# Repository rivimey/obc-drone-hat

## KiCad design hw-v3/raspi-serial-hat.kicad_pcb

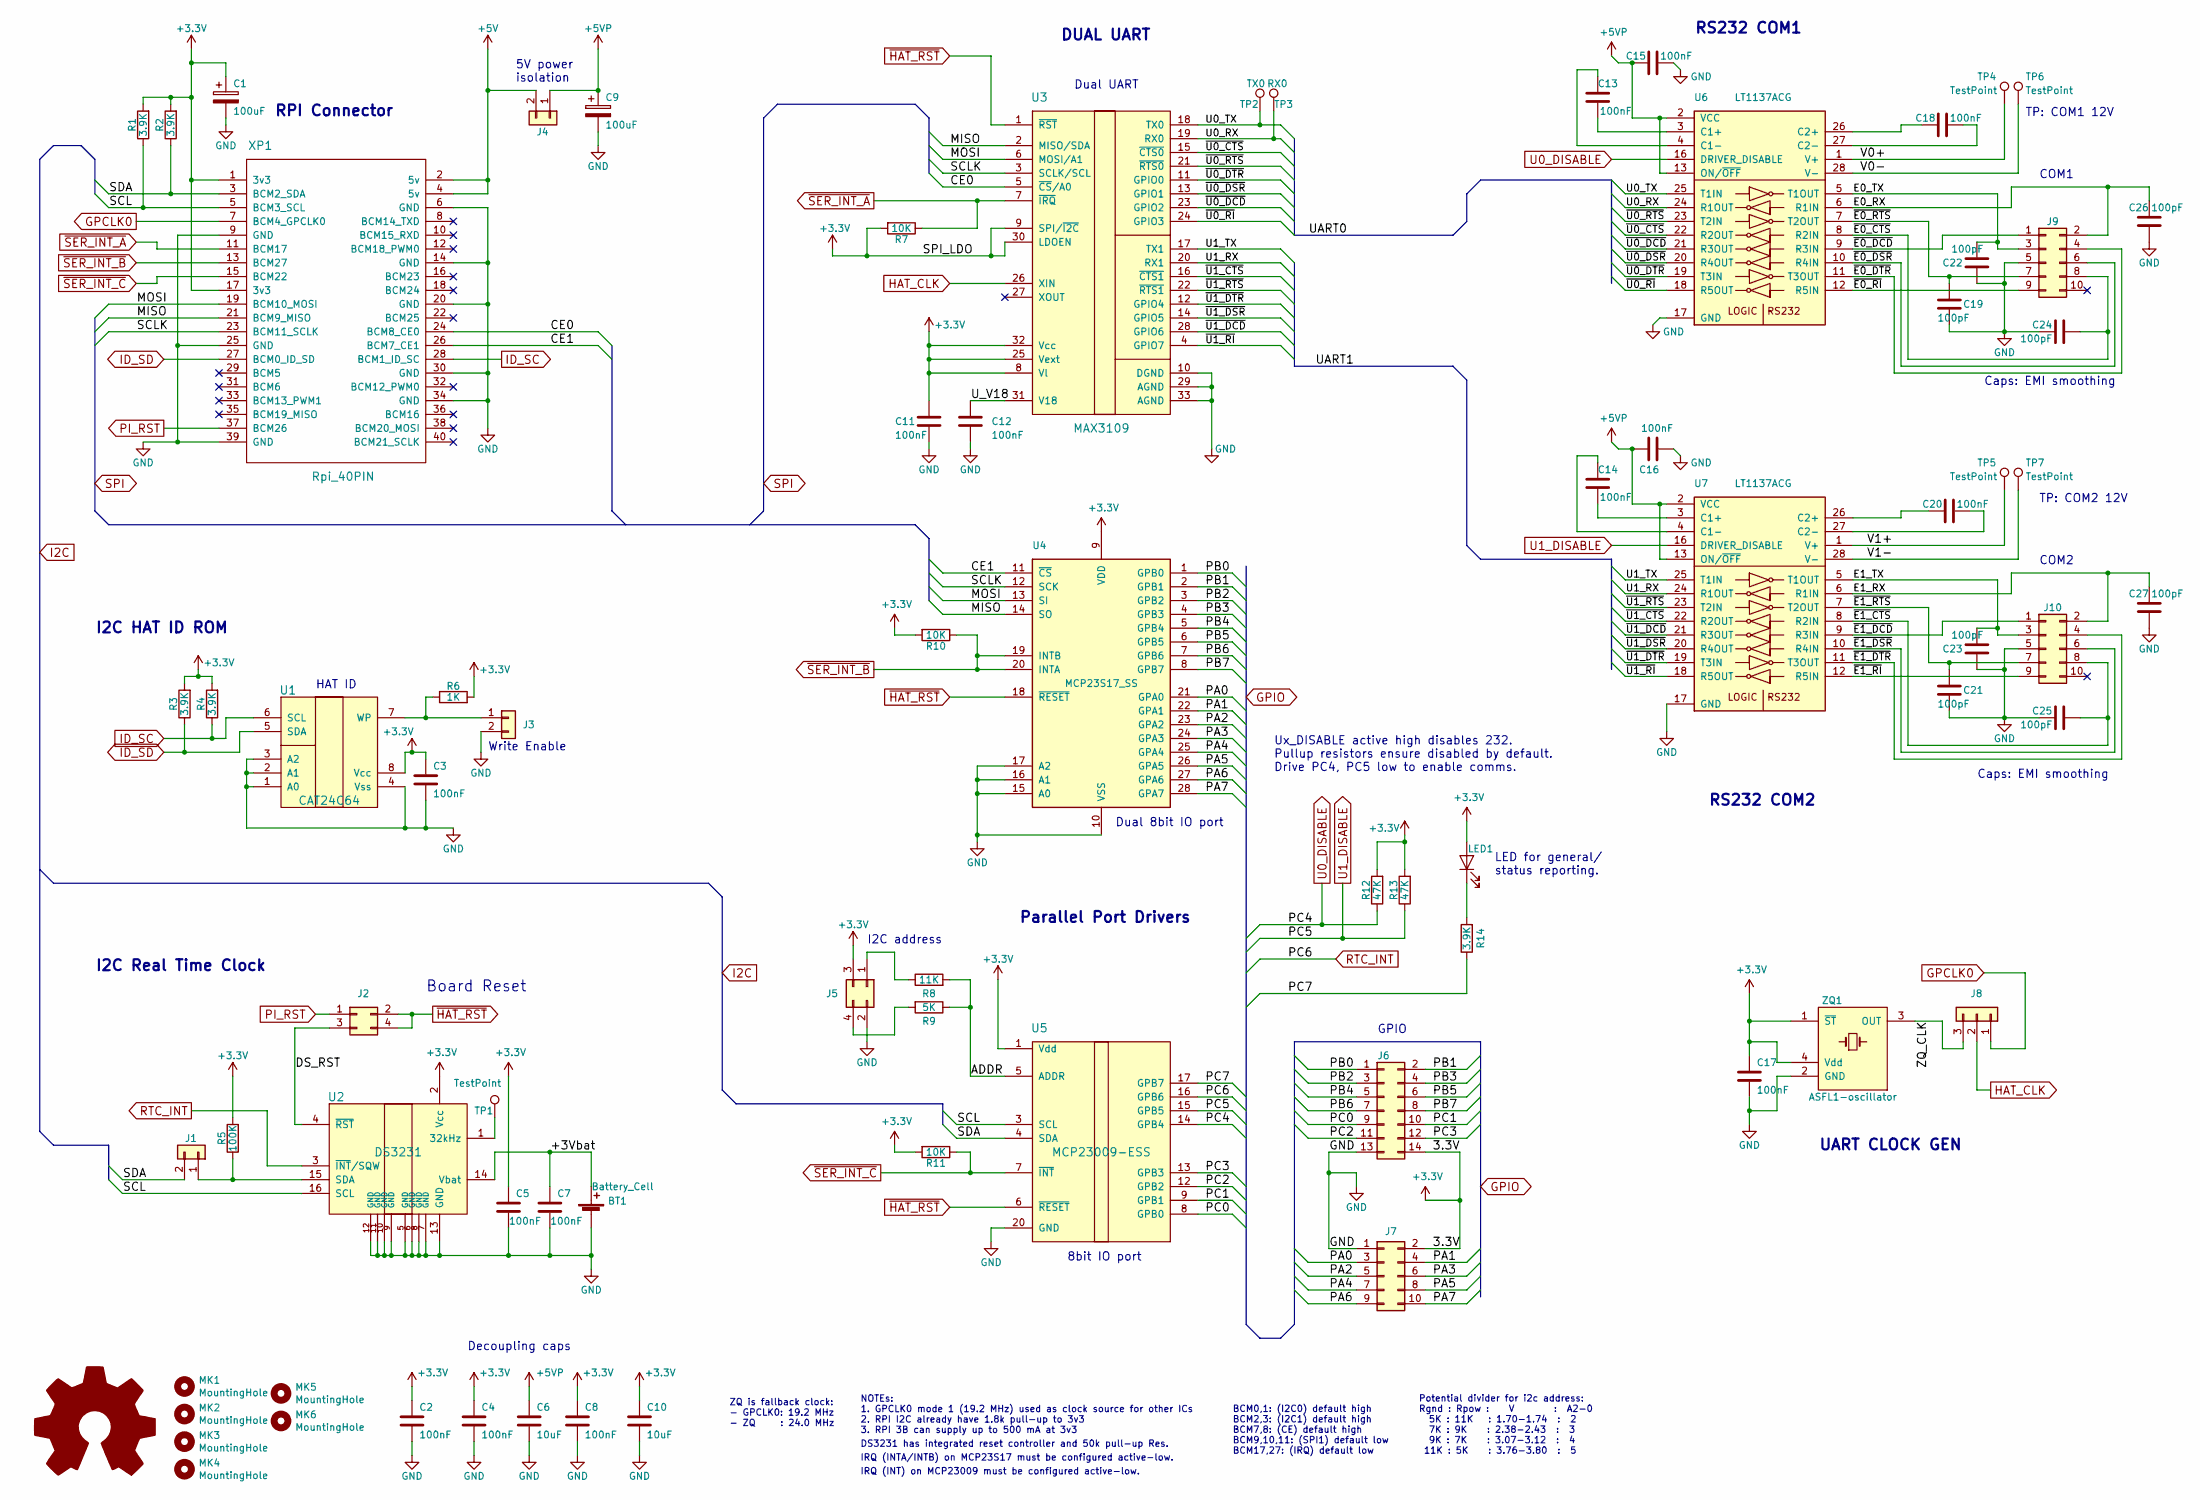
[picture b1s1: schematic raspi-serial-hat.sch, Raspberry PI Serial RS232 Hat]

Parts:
BT1: Battery_Cell; BatteryHolder_Keystone_500; Manuf Part No BAT-HLD-012-SMT
C1, C9: 100uF; CP_EIA-3528-12_Kemet-T_Pad1.50x2.35mm_HandSolder; Manuf Part No T520B107M010ATE070
C2, C3, C4, C5, C7, C8, C11, C12, C13, C14, C15, C16, C17, C18, C20: 100nF; C_0603_1608Metric_Pad1.05x0.95mm_HandSolder; Manuf Part No C0603C104K4RECTU
C6, C10: 10uF; C_0805_2012Metric_Pad1.15x1.40mm_HandSolder; Manuf Part No VJ0805G106KXYTW1BC
C19, C21, C22, C23, C24, C25, C26, C27: 100pF; C_0603_1608Metric_Pad1.05x0.95mm_HandSolder; Manuf Part No 885012206077
J1, J3, J4: Conn_01x02; PinHeader_1x02_P1.27mm_Vertical; Manuf Part No M50-3530242
J2, J5: Conn_02x02; PinHeader_2x02_P1.27mm_Vertical; Manuf Part No M50-3530242
J6: Conn_02x07; PinHeader_2x07_P2.54mm_Vertical; Manuf Part No 54102-S1007LF
J7: Conn_02x05_Odd_Even; PinHeader_2x05_P2.54mm_Vertical
J8: Conn_01x03; PinHeader_1x03_P1.27mm_Vertical; Manuf Part No M50-3530242
J9, J10: Conn_02x05_Odd_Even; IDC-Header_2x05_P2.54mm_Vertical; Manuf Part No 86130105014345E1LF
LED1: LED; LED_0603_1608Metric; Manuf Part No APT1608QGW
MK1, MK2, MK3, MK4, MK5, MK6: MountingHole; M2.5_Mounting_Hole
R1, R2, R3, R4, R14: 3.9K; R_0603_1608Metric_Pad1.05x0.95mm_HandSolder; Manuf Part No CRCW060310K0JNEAC
R5: 100K; R_0603_1608Metric_Pad1.05x0.95mm_HandSolder; Manuf Part No CRCW060310K0JNEAC
R6: 1K; R_0603_1608Metric_Pad1.05x0.95mm_HandSolder; Manuf Part No CRCW060310K0JNEAC
R7, R10, R11: 10K; R_0603_1608Metric_Pad1.05x0.95mm_HandSolder; Manuf Part No CRCW060310K0JNEAC
R8: 11K; R_0603_1608Metric_Pad1.05x0.95mm_HandSolder; Manuf Part No CRCW060310K0JNEAC
R9: 5K; R_0603_1608Metric_Pad1.05x0.95mm_HandSolder; Manuf Part No CRCW060310K0JNEAC
R12, R13: 47K; R_0603_1608Metric_Pad1.05x0.95mm_HandSolder; Manuf Part No CRCW060310K0JNEAC
TP1, TP4, TP5, TP6, TP7: TestPoint; TestPoint_Pad_1.0x1.0mm
TP2: TX0; TestPoint_Pad_1.0x1.0mm
TP3: RX0; TestPoint_Pad_1.0x1.0mm
U1: CAT24C64; SOIC-8_3.9x4.9mm_P1.27mm; Manuf Part No CAT24C64WI-GT3
U2: DS3231; SOIC-16W_7.5x10.3mm_P1.27mm; Manuf Part No DS3231S#T&R
U3: MAX3109; QFN-32-1EP_5x5mm_P0.5mm_EP3.45x3.45mm; Manuf Part No MAX3109ETJ+
U4: MCP23S17_SS; SSOP-28_5.3x10.2mm_P0.65mm; Manuf Part No MCP23S17T-E/SS
U5: MCP23009-ESS; SSOP-20_5.3x7.2mm_P0.65mm; Manuf Part No MCP23009-E/SS
U6, U7: LT1137ACG; SSOP-28_5.3x10.2mm_P0.65mm; Manuf Part No LT1137ACG#PBF
XP1: Rpi_40PIN; RaspberryPi-40Pin_P2.54mm; Manuf Part No 1112
ZQ1: ASFL1-oscillator; Crystal_SMD_Abracon_ABM3B-4Pin_5.0x3.2mm; Manuf Part No ASFL1-24.000MHZ-EC-T

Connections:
+3V3: C1.1, C2.1, C3.1, C4.1, C5.1, C8.1, C10.1, C11.1, C17.1, J5.3, J6.14, J7.2, LED1.2 (A), R1.2, R2.2, R3.2, R4.2, R5.2, R6.2, R7.2, R10.2, R11.2, R12.2, R13.2, U1.8 (Vcc), U2.2 (Vcc), U3.8 (Vl), U3.9 (SPI/~I2C), U3.25 (Vext), U3.30 (LDOEN), U3.32 (Vcc), U4.9 (VDD), U5.1 (Vdd), XP1.1 (3v3), XP1.17 (3v3), ZQ1.1 (~ST), ZQ1.4 (Vdd)
+5V: J4.2, XP1.2 (5v), XP1.4 (5v)
+5VP: C6.1, C9.1, C15.2, C16.1, J4.1, U6.2 (VCC), U6.13 (ON/~OFF), U7.2 (VCC), U7.13 (ON/~OFF)
/+3Vbat: BT1.1 (+), C7.1, U2.14 (Vbat)
/ADDR: R8.2, R9.1, U5.5 (ADDR)
/CE0: U3.5 (~CS~/A0), XP1.24 (BCM8_CE0)
/CE1: U4.11 (~CS~), XP1.26 (BCM7_CE1)
/DS_RST: J2.3, U2.4 (~RST)
/E0_RX: C26.2, J9.2, U6.6 (R1IN)
/E0_TX: C22.2, J9.3, U6.5 (T1OUT)
/E1_RX: C27.2, J10.2, U7.6 (R1IN)
/E1_TX: C23.2, J10.3, U7.5 (T1OUT)
/MISO: U3.2 (MISO/SDA), U4.14 (SO), XP1.21 (BCM9_MISO)
/MOSI: U3.6 (MOSI/A1), U4.13 (SI), XP1.19 (BCM10_MOSI)
/PA0: J7.3, U4.21 (GPA0)
/PA1: J7.4, U4.22 (GPA1)
/PA2: J7.5, U4.23 (GPA2)
/PA3: J7.6, U4.24 (GPA3)
/PA4: J7.7, U4.25 (GPA4)
/PA5: J7.8, U4.26 (GPA5)
/PA6: J7.9, U4.27 (GPA6)
/PA7: J7.10, U4.28 (GPA7)
/PB0: J6.1, U4.1 (GPB0)
/PB1: J6.2, U4.2 (GPB1)
/PB2: J6.3, U4.3 (GPB2)
/PB3: J6.4, U4.4 (GPB3)
/PB4: J6.5, U4.5 (GPB4)
/PB5: J6.6, U4.6 (GPB5)
/PB6: J6.7, U4.7 (GPB6)
/PB7: J6.8, U4.8 (GPB7)
/PC0: J6.9, U5.8 (GPB0)
/PC1: J6.10, U5.9 (GPB1)
/PC2: J6.11, U5.12 (GPB2)
/PC3: J6.12, U5.13 (GPB3)
/PC7: R14.1, U5.17 (GPB7)
/SCL: R1.1, U2.16 (SCL), U5.3 (SCL), XP1.5 (BCM3_SCL)
/SCLK: U3.3 (SCLK/SCL), U4.12 (SCK), XP1.23 (BCM11_SCLK)
/SDA: J1.2, R2.1, U5.4 (SDA), XP1.3 (BCM2_SDA)
/U0_RX: TP3.1, U3.19 (RX0), U6.24 (R1OUT)
/U0_TX: TP2.1, U3.18 (TX0), U6.25 (T1IN)
/U1_RX: U3.20 (RX1), U7.24 (R1OUT)
/U1_TX: U3.17 (TX1), U7.25 (T1IN)
/U_V18: C12.1, U3.31 (V18)
/V0+: TP4.1, U6.1 (V+)
/V0-: TP6.1, U6.28 (V-)
/V1+: TP5.1, U7.1 (V+)
/V1-: TP7.1, U7.28 (V-)
/ZQ_CLK: J8.3, ZQ1.3 (OUT)
/~E0_CTS: C24.2, J9.8, U6.8 (R2IN)
/~E0_DCD: J9.1, U6.9 (R3IN)
/~E0_DSR: J9.6, U6.10 (R4IN)
/~E0_DTR: J9.4, U6.11 (T3OUT)
/~E0_RI: J9.9, U6.12 (R5IN)
/~E0_RTS: C19.2, J9.7, U6.7 (T2OUT)
/~E1_CTS: C25.2, J10.8, U7.8 (R2IN)
/~E1_DCD: J10.1, U7.9 (R3IN)
/~E1_DSR: J10.6, U7.10 (R4IN)
/~E1_DTR: J10.4, U7.11 (T3OUT)
/~E1_RI: J10.9, U7.12 (R5IN)
/~E1_RTS: C21.2, J10.7, U7.7 (T2OUT)
/~U0_CTS: U3.15 (~CTS0), U6.22 (R2OUT)
/~U0_DCD: U3.23 (GPIO2), U6.21 (R3OUT)
/~U0_DSR: U3.13 (GPIO1), U6.20 (R4OUT)
/~U0_DTR: U3.11 (GPIO0), U6.19 (T3IN)
/~U0_RI: U3.24 (GPIO3), U6.18 (R5OUT)
/~U0_RTS: U3.21 (~RTS0), U6.23 (T2IN)
/~U1_CTS: U3.16 (~CTS1), U7.22 (R2OUT)
/~U1_DCD: U3.28 (GPIO6), U7.21 (R3OUT)
/~U1_DSR: U3.14 (GPIO5), U7.20 (R4OUT)
/~U1_DTR: U3.12 (GPIO4), U7.19 (T3IN)
/~U1_RI: U3.4 (GPIO7), U7.18 (R5OUT)
/~U1_RTS: U3.22 (~RTS1), U7.23 (T2IN)
GND: BT1.2 (-), C1.2, C2.2, C3.2, C4.2, C5.2, C6.2, C7.2, C8.2, C9.2, C10.2, C11.2, C12.2, C15.1, C16.2, C17.2, C19.1, C21.1, C22.1, C23.1, C24.1, C25.1, C26.1, C27.1, J3.2, J5.2, J6.13, J7.1, J9.5, J10.5, U1.1 (A0), U1.2 (A1), U1.3 (A2), U1.4 (Vss), U2.5 (GND), U2.6 (GND), U2.7 (GND), U2.8 (GND), U2.9 (GND), U2.10 (GND), U2.11 (GND), U2.12 (GND), U2.13 (GND), U3.10 (DGND), U3.29 (AGND), U3.33 (AGND), U4.10 (VSS), U4.15 (A0), U4.16 (A1), U4.17 (A2), U5.20 (GND), U6.17 (GND), U7.17 (GND), XP1.6 (GND), XP1.9 (GND), XP1.14 (GND), XP1.20 (GND), XP1.25 (GND), XP1.30 (GND), XP1.34 (GND), XP1.39 (GND), ZQ1.2 (GND)
GPCLK0: J8.1, XP1.7 (BCM4_GPCLK0)
HAT_CLK: J8.2, U3.26 (XIN)
ID_SC: R4.1, U1.6 (SCL), XP1.28 (BCM1_ID_SC)
ID_SD: R3.1, U1.5 (SDA), XP1.27 (BCM0_ID_SD)
unnamed: C13.1, U6.3 (C1+)
unnamed: C13.2, U6.4 (C1-)
unnamed: C14.1, U7.3 (C1+)
unnamed: C14.2, U7.4 (C1-)
unnamed: C18.1, U6.27 (C2-)
unnamed: C18.2, U6.26 (C2+)
unnamed: C20.1, U7.27 (C2-)
unnamed: C20.2, U7.26 (C2+)
unnamed: J1.1, R5.1, U2.15 (SDA)
unnamed: J3.1, R6.1, U1.7 (WP)
unnamed: J5.1, R8.1
unnamed: J5.4, R9.2
unnamed: LED1.1 (K), R14.2
unnamed: TP1.1, U2.1 (32kHz)
PI_RST: J2.1, XP1.37 (BCM26)
RTC_INT: U2.3 (~INT~/SQW), U5.16 (GPB6)
U0_DISABLE: R12.1, U5.14 (GPB4), U6.16 (DRIVER_DISABLE)
U1_DISABLE: R13.1, U5.15 (GPB5), U7.16 (DRIVER_DISABLE)
~HAT_RST: J2.2, J2.4, U3.1 (~RST), U4.18 (~RESET~), U5.6 (~RESET)
~SER_INT_A: R7.1, U3.7 (~IRQ), XP1.11 (BCM17)
~SER_INT_B: R10.1, U4.19 (INTB), U4.20 (INTA), XP1.13 (BCM27)
~SER_INT_C: R11.1, U5.7 (~INT), XP1.15 (BCM22)

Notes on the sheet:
DS3231 has integrated reset controller and 50k pull-up Res.
NOTEs: 1. GPCLK0 mode 1 (19.2 MHz) used as clock source for other ICs 2. RPI I2C already have 1.8k pull-up to 3v3 3. RPI 3B can supply up to 500 mA at 3v3
ZQ is fallback clock: - GPCLK0: 19.2 MHz - ZQ : 24.0 MHz
HAT ID
Decoupling caps
GPIO
Dual UART
TP: COM1 12V
Dual 8bit IO port
8bit IO port
RPI Connector
IRQ (INTA/INTB) on MCP23S17 must be configured active-low.
IRQ (INT) on MCP23009 must be configured active-low.
I2C address
COM1
BCM0,1: (I2C0) default high BCM2,3: (I2C1) default high BCM7,8: (CE) default high BCM9,10,11: (SPI1) default low BCM17,27: (IRQ) default low
5V power isolation
I2C HAT ID ROM
RS232 COM1
RS232 COM2
Caps: EMI smoothing
COM2
TP: COM2 12V
UART CLOCK GEN
DUAL UART
Parallel Port Drivers
Write Enable
Board Reset
Ux_DISABLE active high disables 232. Pullup resistors ensure disabled by default. Drive PC4, PC5 low to enable comms.
LED for general/ status reporting.
I2C Real Time Clock
Potential divider for i2c address: Rgnd : Rpow : V : A2-0 5K : 11K : 1.70-1.74 : 2 7K : 9K : 2.38-2.43 : 3 9K : 7K : 3.07-3.12 : 4 11K : 5K : 3.76-3.80 : 5

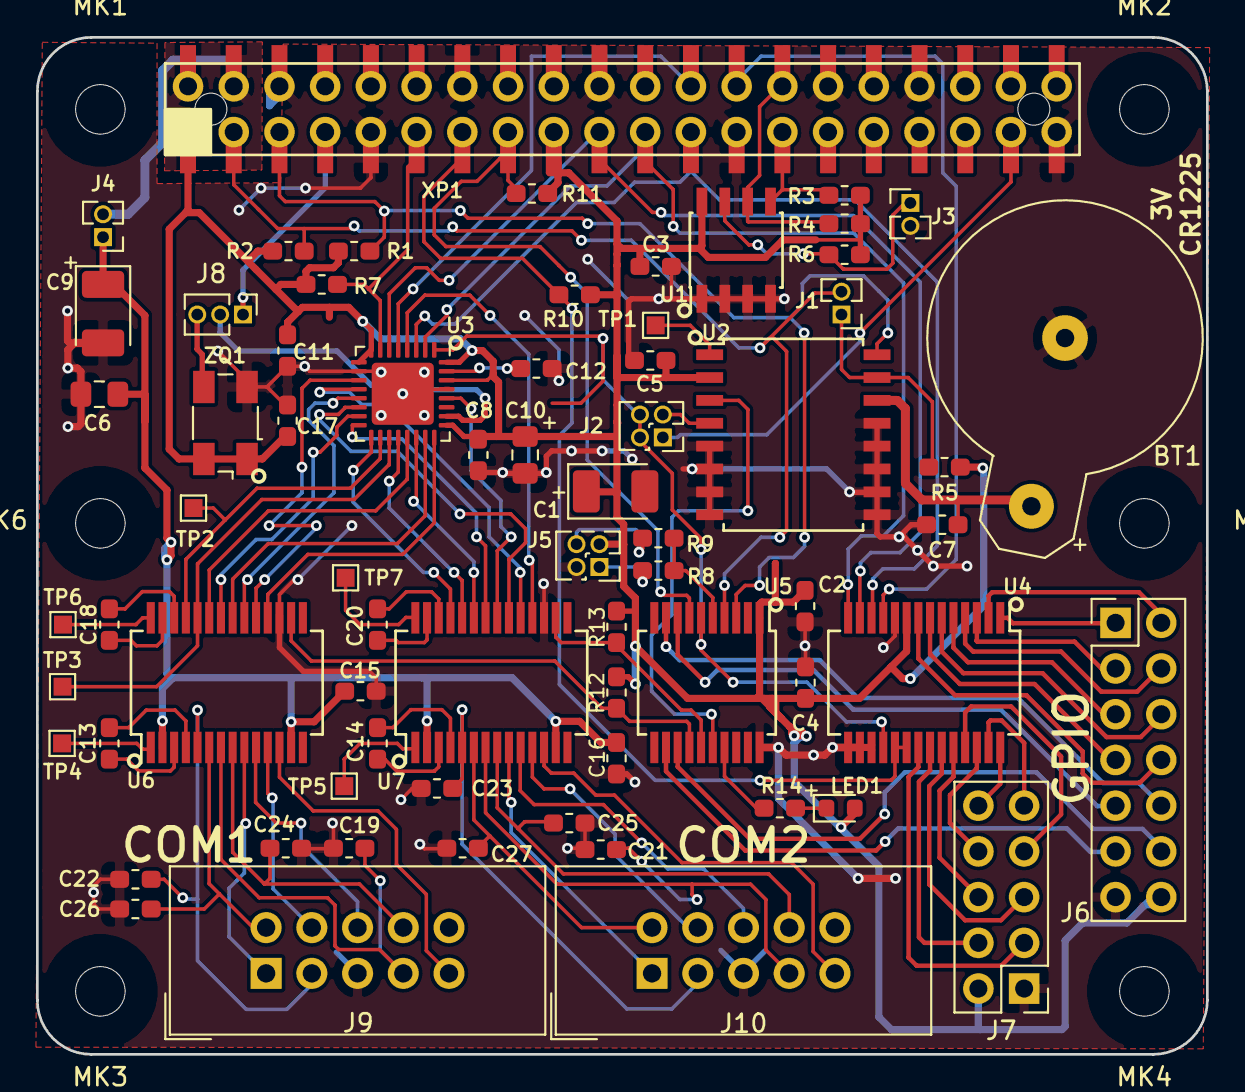
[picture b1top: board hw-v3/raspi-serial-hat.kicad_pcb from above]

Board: 2 copper layers, 65.0 x 56.5 mm, 75 parts (0 on the bottom side), 99 nets.

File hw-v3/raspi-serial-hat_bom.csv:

Source,/Users/ruth/Electronics/raspi-serial-hat/hw-v3/raspi-serial-hat.sch
Kicad Rev,Eeschema (5.1.4-0)
Generated Date,Tuesday, 15 October 2019 at 23:43:15

Title,Raspberry PI Serial RS232 Hat
Company,IvimeyCom
Revision,3
Date Issue,2019-10-08
Comment,IC-SERHAT-v3

Reference,Value,Cost/item,Manuf Part No,Manufacturer,Stock Number,Supplier,Library,Library Ref
BT1,Battery_Cell,0.221,BAT-HLD-012-SMT,Linx Technologies,712-BAT-HLD-012-SMT,Mouser,Device,Battery_Cell
C1,100uF,1.14,T520B107M010ATE070,KEMET,80-T520B107M10ATE070 ,Mouser,Device,CP
C10,10uF,0.30,VJ0805G106KXYTW1BC ,Vishay / Vitramon,77-VJ805G106KXYTW1BC ,Mouser,Device,C
C11,100nF,0.084,C0603C104K4RECTU,KEMET,80-C0603C104K4RECTU,Mouser,Device,C
C12,100nF,0.084,C0603C104K4RECTU,KEMET,80-C0603C104K4RECTU,Mouser,Device,C
C13,100nF,0.084,C0603C104K4RECTU,KEMET,80-C0603C104K4RECTU,Mouser,Device,C
C14,100nF,0.084,C0603C104K4RECTU,KEMET,80-C0603C104K4RECTU,Mouser,Device,C
C15,100nF,0.084,C0603C104K4RECTU,KEMET,80-C0603C104K4RECTU,Mouser,Device,C
C16,100nF,0.084,C0603C104K4RECTU,KEMET,80-C0603C104K4RECTU,Mouser,Device,C
C17,100nF,0.084,C0603C104K4RECTU,KEMET,80-C0603C104K4RECTU,Mouser,Device,C
C18,100nF,0.084,C0603C104K4RECTU,KEMET,80-C0603C104K4RECTU,Mouser,Device,C
C19,100pF,0.035,885012206077,Wurth Electronics,710-885012206077,Mouser,Device,C
C2,100nF,0.084,C0603C104K4RECTU,KEMET,80-C0603C104K4RECTU,Mouser,Device,C
C20,100nF,0.084,C0603C104K4RECTU,KEMET,80-C0603C104K4RECTU,Mouser,Device,C
C21,100pF,0.035,885012206077,Wurth Electronics,710-885012206077,Mouser,Device,C
C22,100pF,0.035,885012206077,Wurth Electronics,710-885012206077,Mouser,Device,C
C23,100pF,0.035,885012206077,Wurth Electronics,710-885012206077,Mouser,Device,C
C24,100pF,0.035,885012206077,Wurth Electronics,710-885012206077,Mouser,Device,C
C25,100pF,0.035,885012206077,Wurth Electronics,710-885012206077,Mouser,Device,C
C26,100pF,0.035,885012206077,Wurth Electronics,710-885012206077,Mouser,Device,C
C27,100pF,0.035,885012206077,Wurth Electronics,710-885012206077,Mouser,Device,C
C3,100nF,0.084,C0603C104K4RECTU,KEMET,80-C0603C104K4RECTU,Mouser,Device,C
C4,100nF,0.084,C0603C104K4RECTU,KEMET,80-C0603C104K4RECTU,Mouser,Device,C
C5,100nF,0.084,C0603C104K4RECTU,KEMET,80-C0603C104K4RECTU,Mouser,Device,C
C6,10uF,0.30,VJ0805G106KXYTW1BC ,Vishay / Vitramon,77-VJ805G106KXYTW1BC ,Mouser,Device,C
C7,100nF,0.084,C0603C104K4RECTU,KEMET,80-C0603C104K4RECTU,Mouser,Device,C
C8,100nF,0.084,C0603C104K4RECTU,KEMET,80-C0603C104K4RECTU,Mouser,Device,C
C9,100uF,1.14,T520B107M010ATE070,KEMET,80-T520B107M10ATE070 ,Mouser,Device,CP
J1,Conn_01x02,0.084,M50-3530242,Harwin,855-M50-3530242,Mouser,Connector_Generic,Conn_01x02
J10,Conn_02x05_Odd_Even,0.343,86130105014345E1LF,Amphenol FCI,649-861315014345E1LF,Mouser,Connector_Generic,Conn_02x05_Odd_Even
J2,Conn_02x02,0.084,M50-3530242,Harwin,855-M50-3530242,Mouser,Connector_Generic,Conn_02x02_Odd_Even
J3,Conn_01x02,0.084,M50-3530242,Harwin,855-M50-3530242,Mouser,Connector_Generic,Conn_01x02
J4,Conn_01x02,0.084,M50-3530242,Harwin,855-M50-3530242,Mouser,Connector_Generic,Conn_01x02
J5,Conn_02x02,0.084,M50-3530242,Harwin,855-M50-3530242,Mouser,Connector_Generic,Conn_02x02_Odd_Even
J6,Conn_02x07,0.481,54102-S1007LF,Amphenol FCI,649-54102-S1007LF,Mouser,Connector_Generic,Conn_02x07_Odd_Even
J7,Conn_02x05_Odd_Even,Connector_Generic,Conn_02x05_Odd_Even
J8,Conn_01x03,0.084,M50-3530242,Harwin,855-M50-3530242,Mouser,Connector_Generic,Conn_01x03
J9,Conn_02x05_Odd_Even,0.343,86130105014345E1LF,Amphenol FCI,649-861315014345E1LF,Mouser,Connector_Generic,Conn_02x05_Odd_Even
LED1,LED,Device,LED
R1,3.9K,0.076,CRCW060310K0JNEAC,Vishay,71-CRCW060310K0JNEAC,Mouser,Device,R
R10,10K,0.076,CRCW060310K0JNEAC,Vishay,71-CRCW060310K0JNEAC,Mouser,Device,R
R11,10K,0.076,CRCW060310K0JNEAC,Vishay,71-CRCW060310K0JNEAC,Mouser,Device,R
R12,47K,0.076,CRCW060310K0JNEAC,Vishay,71-CRCW060310K0JNEAC,Mouser,Device,R
R13,47K,0.076,CRCW060310K0JNEAC,Vishay,71-CRCW060310K0JNEAC,Mouser,Device,R
R14,3.9K,0.076,CRCW060310K0JNEAC,Vishay,71-CRCW060310K0JNEAC,Mouser,Device,R
R2,3.9K,0.076,CRCW060310K0JNEAC,Vishay,71-CRCW060310K0JNEAC,Mouser,Device,R
R3,3.9K,0.076,CRCW060310K0JNEAC,Vishay,71-CRCW060310K0JNEAC,Mouser,Device,R
R4,3.9K,0.076,CRCW060310K0JNEAC,Vishay,71-CRCW060310K0JNEAC,Mouser,Device,R
R5,100K,0.076,CRCW060310K0JNEAC,Vishay,71-CRCW060310K0JNEAC,Mouser,Device,R
R6,1K,0.076,CRCW060310K0JNEAC,Vishay,71-CRCW060310K0JNEAC,Mouser,Device,R
R7,10K,0.076,CRCW060310K0JNEAC,Vishay,71-CRCW060310K0JNEAC,Mouser,Device,R
R8,11K,0.076,CRCW060310K0JNEAC,Vishay,71-CRCW060310K0JNEAC,Mouser,Device,R
R9,5K,0.076,CRCW060310K0JNEAC,Vishay,71-CRCW060310K0JNEAC,Mouser,Device,R
U1,CAT24C64,,CAT24C64WI-GT3,ON Semiconductor,698-CAT24C64WI-GT3,Mouser,hat-ic,CAT24
U2,DS3231,6.00,DS3231S#T&R,Maxim Integrated,700-DS3231S#T&R- ,Mouser,hat-ic,DS3231
U3,MAX3109,5.21,MAX3109ETJ+,Maxim Integrated,700-MAX3109ETJ+,Mouser,hat-ic,MAX3109
U4,MCP23S17_SS,1.03,MCP23S17T-E/SS,Microchip Technology,579-MCP23S17T-E/SS,Mouser,Interface_Expansion,MCP23S17_SS
U5,MCP23009-ESS,0.882,MCP23009-E/SS,Microchip Technology,579-MCP23009-E/SS,Mouser,hat-ic,MCP23009-ESS
U6,LT1137ACG,6.07,LT1137ACG#PBF,Analog Devices,584-LT1137ACG#PBF,Mouser,uarts,LT1137ACG
U7,LT1137ACG,6.07,LT1137ACG#PBF,Analog Devices,584-LT1137ACG#PBF,Mouser,uarts,LT1137ACG
XP1,Rpi_40PIN,1.49,1112,Adafruit,485-1112,Mouser,rpi-conn,Rpi_40PIN
ZQ1,ASFL1-oscillator,0.944,ASFL1-24.000MHZ-EC-T,ABRACON,815-ASFL1-24.0-EC-T,Mouser,hat-ic,ASFL1-oscillator

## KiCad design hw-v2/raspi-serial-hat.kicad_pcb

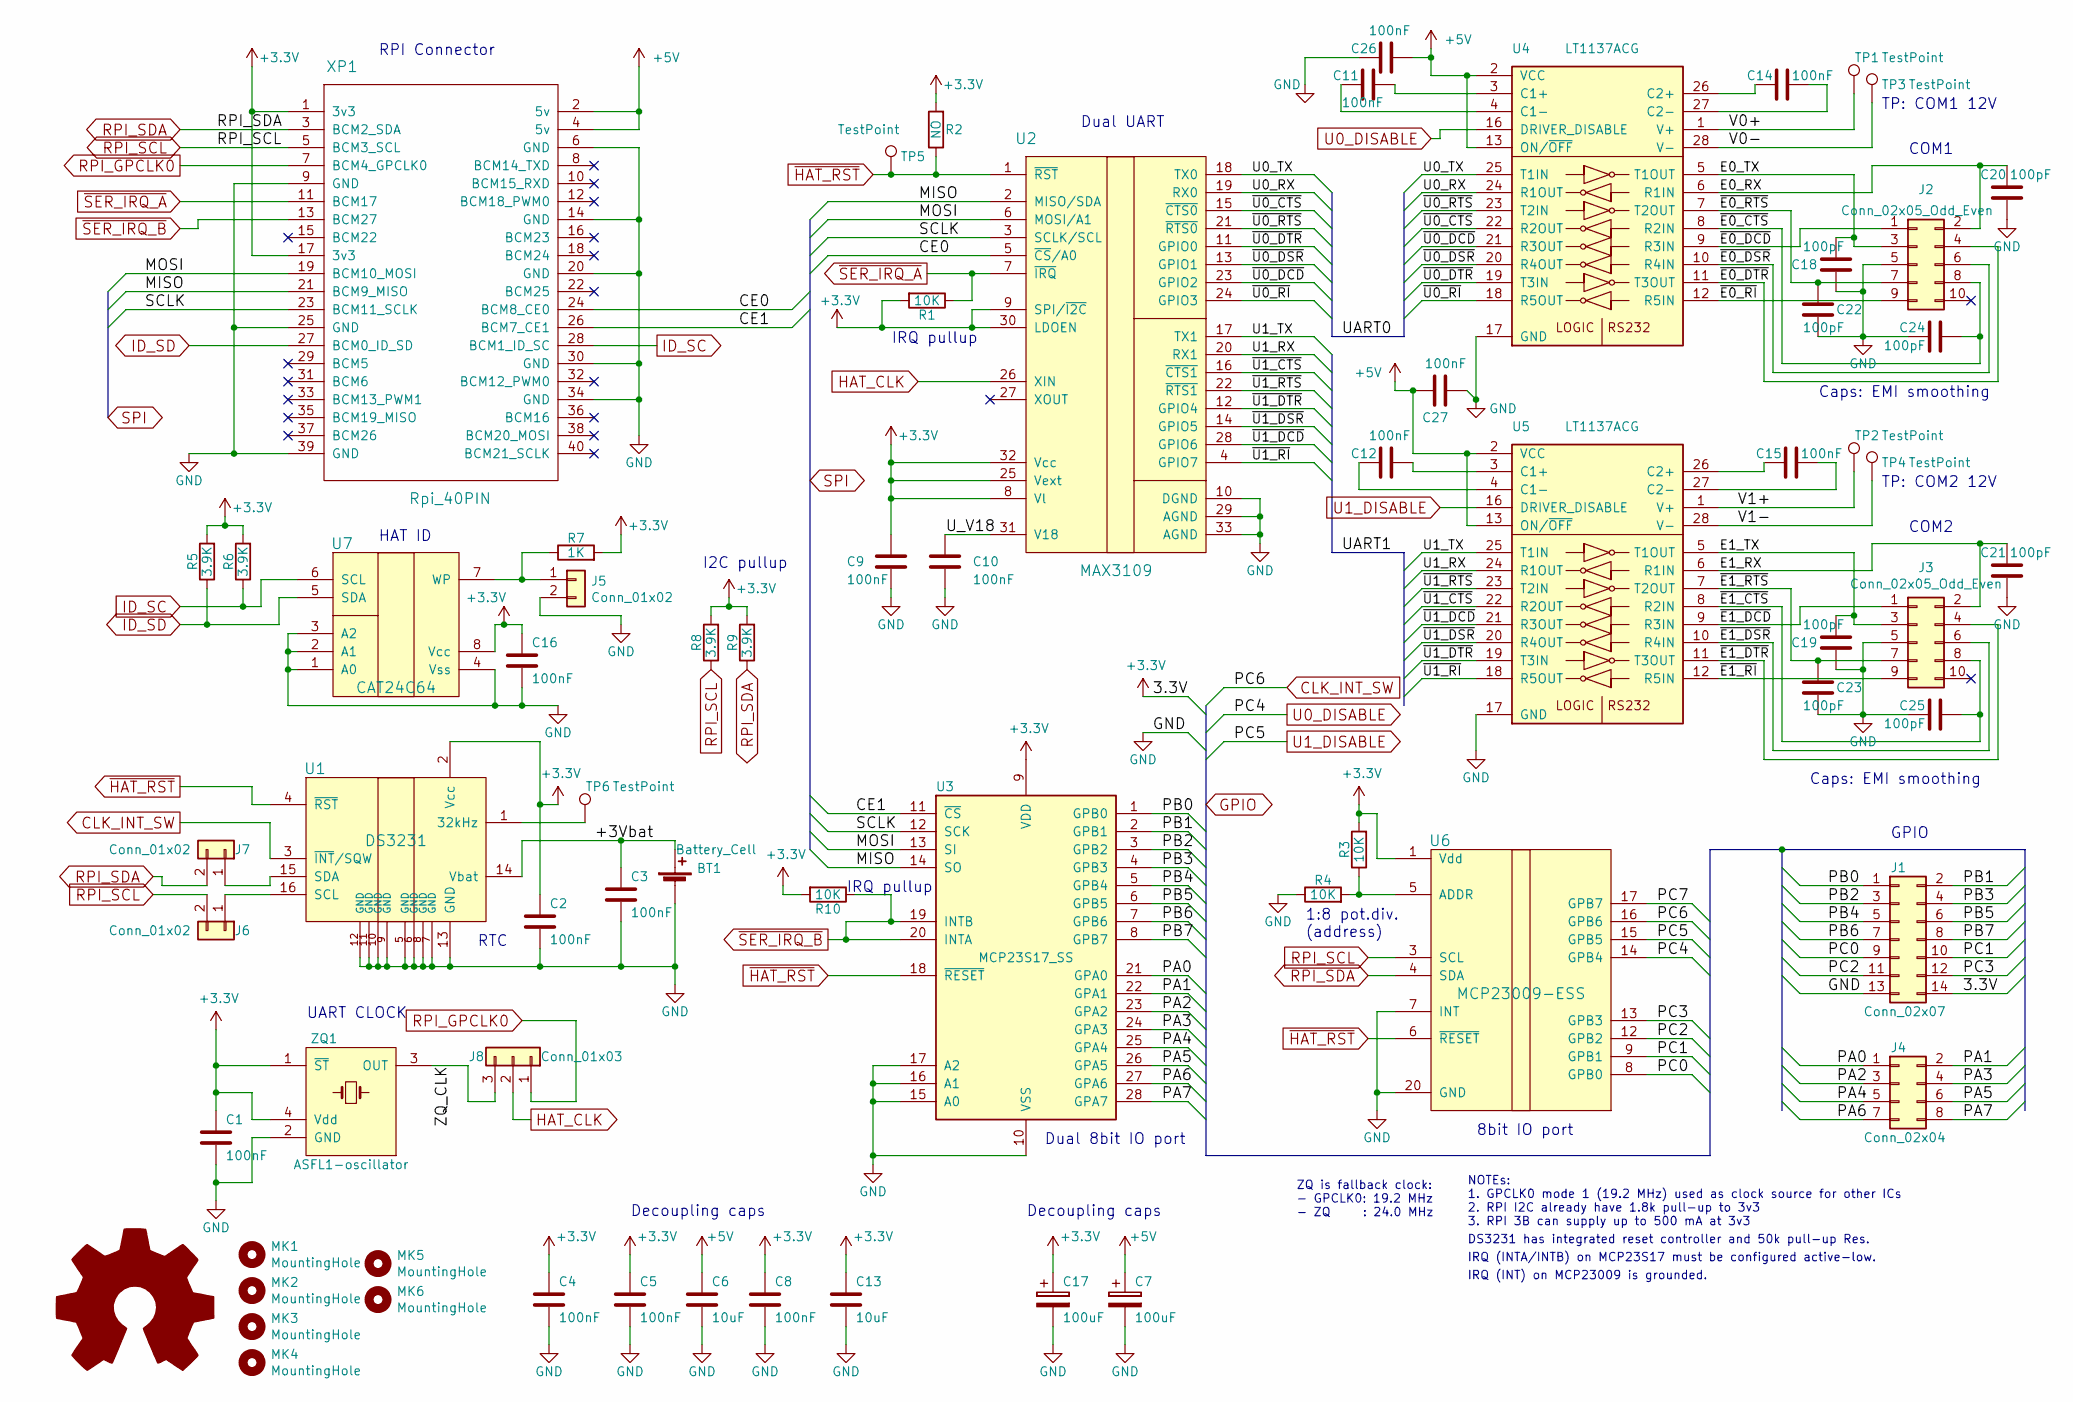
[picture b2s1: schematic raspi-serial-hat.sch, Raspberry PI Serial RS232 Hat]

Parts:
BT1: Battery_Cell; BatteryHolder_LINX_BAT-HLD-012-SMT; Manuf Part No BAT-HLD-012-SMT
C1, C2, C3, C4, C5, C8, C9, C10, C11, C12, C14, C15, C16, C26, C27: 100nF; C_0603_1608Metric_Pad1.05x0.95mm_HandSolder; Manuf Part No C0603C104K4RECTU
C6, C13: 10uF; C_0805_2012Metric_Pad1.15x1.40mm_HandSolder; Manuf Part No VJ0805G106KXYTW1BC
C7, C17: 100uF; CP_EIA-3528-12_Kemet-T_Pad1.50x2.35mm_HandSolder; Manuf Part No T520B107M010ATE070
C18, C19, C20, C21, C22, C23, C24, C25: 100pF; C_0603_1608Metric_Pad1.05x0.95mm_HandSolder; Manuf Part No 885012206077
J1: Conn_02x07; PinHeader_2x07_P2.54mm_Vertical; Manuf Part No 54102-S1007LF
J2, J3: Conn_02x05_Odd_Even; IDC-Header_2x05_P2.54mm_Vertical; Manuf Part No 86130105014345E1LF
J4: Conn_02x04; PinHeader_2x04_P2.54mm_Vertical; Manuf Part No 68602-408HLF
J5, J6, J7: Conn_01x02; PinHeader_1x02_P1.27mm_Vertical; Manuf Part No M50-3530242
J8: Conn_01x03; PinHeader_1x03_P1.27mm_Vertical; Manuf Part No M50-3530242
MK1, MK2, MK3, MK4, MK5, MK6: MountingHole; M2.5_Mounting_Hole
R1, R3, R4, R10: 10K; R_0603_1608Metric_Pad1.05x0.95mm_HandSolder; Manuf Part No CRCW060310K0JNEAC
R2: NO; R_0603_1608Metric_Pad1.05x0.95mm_HandSolder; Manuf Part No DNF
R5, R6, R8, R9: 3.9K; R_0603_1608Metric_Pad1.05x0.95mm_HandSolder; Manuf Part No CRCW060310K0JNEAC
R7: 1K; R_0603_1608Metric_Pad1.05x0.95mm_HandSolder; Manuf Part No CRCW060310K0JNEAC
TP1, TP2, TP3, TP4, TP5, TP6: TestPoint; TestPoint_Pad_1.0x1.0mm
U1: DS3231; SOIC-16W_7.5x10.3mm_P1.27mm; Manuf Part No DS3231S#T&R
U2: MAX3109; QFN-32-1EP_5x5mm_P0.5mm_EP3.45x3.45mm; Manuf Part No MAX3109ETJ+
U3: MCP23S17_SS; SSOP-28_5.3x10.2mm_P0.65mm; Manuf Part No MCP23S17T-E/SS
U4, U5: LT1137ACG; SSOP-28_5.3x10.2mm_P0.65mm; Manuf Part No LT1137ACG#PBF
U6: MCP23009-ESS; SSOP-20_5.3x7.2mm_P0.65mm; Manuf Part No MCP23009-E/SS
U7: CAT24C64; SOIC-8_3.9x4.9mm_P1.27mm; Manuf Part No CAT24C64WI-GT3
XP1: Rpi_40PIN; RaspberryPi-40Pin_P2.54mm; Manuf Part No 1112
ZQ1: ASFL1-oscillator; Crystal_SMD_Abracon_ABM3B-4Pin_5.0x3.2mm; Manuf Part No ASFL1-24.000MHZ-EC-T

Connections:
+3V3: C1.1, C2.1, C4.1, C5.1, C8.1, C9.1, C13.1, C16.1, C17.1, J1.14, R1.2, R2.2, R3.2, R5.2, R6.2, R7.2, R8.2, R9.2, R10.2, U1.2 (Vcc), U2.8 (Vl), U2.9 (SPI/~I2C), U2.25 (Vext), U2.30 (LDOEN), U2.32 (Vcc), U3.9 (VDD), U6.1 (Vdd), U7.8 (Vcc), XP1.1 (3v3), XP1.17 (3v3), ZQ1.1 (~ST), ZQ1.4 (Vdd)
+5V: C6.1, C7.1, C26.1, C27.1, U4.2 (VCC), U4.13 (ON/~OFF), U5.2 (VCC), U5.13 (ON/~OFF), XP1.2 (5v), XP1.4 (5v)
/+3Vbat: BT1.1 (+), C3.1, U1.14 (Vbat)
/CE0: U2.5 (~CS~/A0), XP1.24 (BCM8_CE0)
/CE1: U3.11 (~CS~), XP1.26 (BCM7_CE1)
/E0_RX: C20.2, J2.2, U4.6 (R1IN)
/E0_TX: C18.2, J2.3, U4.5 (T1OUT)
/E1_RX: C21.2, J3.2, U5.6 (R1IN)
/E1_TX: C19.2, J3.3, U5.5 (T1OUT)
/MISO: U2.2 (MISO/SDA), U3.14 (SO), XP1.21 (BCM9_MISO)
/MOSI: U2.6 (MOSI/A1), U3.13 (SI), XP1.19 (BCM10_MOSI)
/PA0: J4.1, U3.21 (GPA0)
/PA1: J4.2, U3.22 (GPA1)
/PA2: J4.3, U3.23 (GPA2)
/PA3: J4.4, U3.24 (GPA3)
/PA4: J4.5, U3.25 (GPA4)
/PA5: J4.6, U3.26 (GPA5)
/PA6: J4.7, U3.27 (GPA6)
/PA7: J4.8, U3.28 (GPA7)
/PB0: J1.1, U3.1 (GPB0)
/PB1: J1.2, U3.2 (GPB1)
/PB2: J1.3, U3.3 (GPB2)
/PB3: J1.4, U3.4 (GPB3)
/PB4: J1.5, U3.5 (GPB4)
/PB5: J1.6, U3.6 (GPB5)
/PB6: J1.7, U3.7 (GPB6)
/PB7: J1.8, U3.8 (GPB7)
/PC0: J1.9, U6.8 (GPB0)
/PC1: J1.10, U6.9 (GPB1)
/PC2: J1.11, U6.12 (GPB2)
/PC3: J1.12, U6.13 (GPB3)
/SCLK: U2.3 (SCLK/SCL), U3.12 (SCK), XP1.23 (BCM11_SCLK)
/U0_RX: U2.19 (RX0), U4.24 (R1OUT)
/U0_TX: U2.18 (TX0), U4.25 (T1IN)
/U1_RX: U2.20 (RX1), U5.24 (R1OUT)
/U1_TX: U2.17 (TX1), U5.25 (T1IN)
/U_V18: C10.1, U2.31 (V18)
/V0+: TP1.1, U4.1 (V+)
/V0-: TP3.1, U4.28 (V-)
/V1+: TP2.1, U5.1 (V+)
/V1-: TP4.1, U5.28 (V-)
/ZQ_CLK: J8.3, ZQ1.3 (OUT)
/~E0_CTS: C24.2, J2.8, U4.8 (R2IN)
/~E0_DCD: J2.1, U4.9 (R3IN)
/~E0_DSR: J2.6, U4.10 (R4IN)
/~E0_DTR: J2.4, U4.11 (T3OUT)
/~E0_RI: J2.9, U4.12 (R5IN)
/~E0_RTS: C22.2, J2.7, U4.7 (T2OUT)
/~E1_CTS: C25.2, J3.8, U5.8 (R2IN)
/~E1_DCD: J3.1, U5.9 (R3IN)
/~E1_DSR: J3.6, U5.10 (R4IN)
/~E1_DTR: J3.4, U5.11 (T3OUT)
/~E1_RI: J3.9, U5.12 (R5IN)
/~E1_RTS: C23.2, J3.7, U5.7 (T2OUT)
/~U0_CTS: U2.15 (~CTS0), U4.22 (R2OUT)
/~U0_DCD: U2.23 (GPIO2), U4.21 (R3OUT)
/~U0_DSR: U2.13 (GPIO1), U4.20 (R4OUT)
/~U0_DTR: U2.11 (GPIO0), U4.19 (T3IN)
/~U0_RI: U2.24 (GPIO3), U4.18 (R5OUT)
/~U0_RTS: U2.21 (~RTS0), U4.23 (T2IN)
/~U1_CTS: U2.16 (~CTS1), U5.22 (R2OUT)
/~U1_DCD: U2.28 (GPIO6), U5.21 (R3OUT)
/~U1_DSR: U2.14 (GPIO5), U5.20 (R4OUT)
/~U1_DTR: U2.12 (GPIO4), U5.19 (T3IN)
/~U1_RI: U2.4 (GPIO7), U5.18 (R5OUT)
/~U1_RTS: U2.22 (~RTS1), U5.23 (T2IN)
CLK_INT_SW: U1.3 (~INT~/SQW), U6.16 (GPB6)
GND: BT1.2 (-), C1.2, C2.2, C3.2, C4.2, C5.2, C6.2, C7.2, C8.2, C9.2, C10.2, C13.2, C16.2, C17.2, C18.1, C19.1, C20.1, C21.1, C22.1, C23.1, C24.1, C25.1, C26.2, C27.2, J1.13, J2.5, J3.5, J5.2, R4.1, U1.5 (GND), U1.6 (GND), U1.7 (GND), U1.8 (GND), U1.9 (GND), U1.10 (GND), U1.11 (GND), U1.12 (GND), U1.13 (GND), U2.10 (DGND), U2.29 (AGND), U2.33 (AGND), U3.10 (VSS), U3.15 (A0), U3.16 (A1), U3.17 (A2), U4.17 (GND), U5.17 (GND), U6.7 (INT), U6.20 (GND), U7.1 (A0), U7.2 (A1), U7.3 (A2), U7.4 (Vss), XP1.6 (GND), XP1.9 (GND), XP1.14 (GND), XP1.20 (GND), XP1.25 (GND), XP1.30 (GND), XP1.34 (GND), XP1.39 (GND), ZQ1.2 (GND)
HAT_CLK: J8.2, U2.26 (XIN)
ID_SC: R6.1, U7.6 (SCL), XP1.28 (BCM1_ID_SC)
ID_SD: R5.1, U7.5 (SDA), XP1.27 (BCM0_ID_SD)
unnamed: C11.1, U4.3 (C1+)
unnamed: C11.2, U4.4 (C1-)
unnamed: C12.1, U5.3 (C1+)
unnamed: C12.2, U5.4 (C1-)
unnamed: C14.1, U4.27 (C2-)
unnamed: C14.2, U4.26 (C2+)
unnamed: C15.1, U5.27 (C2-)
unnamed: C15.2, U5.26 (C2+)
unnamed: J5.1, R7.1, U7.7 (WP)
unnamed: J6.1, U1.16 (SCL)
unnamed: J7.1, U1.15 (SDA)
unnamed: R3.1, R4.2, U6.5 (ADDR)
unnamed: TP6.1, U1.1 (32kHz)
RPI_GPCLK0: J8.1, XP1.7 (BCM4_GPCLK0)
RPI_SCL: J6.2, R8.1, U6.3 (SCL), XP1.5 (BCM3_SCL)
RPI_SDA: J7.2, R9.1, U6.4 (SDA), XP1.3 (BCM2_SDA)
U0_DISABLE: U4.16 (DRIVER_DISABLE), U6.14 (GPB4)
U1_DISABLE: U5.16 (DRIVER_DISABLE), U6.15 (GPB5)
~HAT_RST: R2.1, TP5.1, U1.4 (~RST), U2.1 (~RST), U3.18 (~RESET~), U6.6 (~RESET)
~SER_IRQ_A: R1.1, U2.7 (~IRQ), XP1.11 (BCM17)
~SER_IRQ_B: R10.1, U3.19 (INTB), U3.20 (INTA), XP1.13 (BCM27)

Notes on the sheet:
DS3231 has integrated reset controller and 50k pull-up Res.
NOTEs: 1. GPCLK0 mode 1 (19.2 MHz) used as clock source for other ICs 2. RPI I2C already have 1.8k pull-up to 3v3 3. RPI 3B can supply up to 500 mA at 3v3
ZQ is fallback clock: - GPCLK0: 19.2 MHz - ZQ : 24.0 MHz
I2C pullup
HAT ID
RTC
UART CLOCK
Decoupling caps
GPIO
Dual UART
TP: COM1 12V
TP: COM2 12V
Dual 8bit IO port
8bit IO port
RPI Connector
IRQ pullup
IRQ (INTA/INTB) on MCP23S17 must be configured active-low.
IRQ (INT) on MCP23009 is grounded.
1:8 pot.div. (address)
COM2
COM1
Caps: EMI smoothing

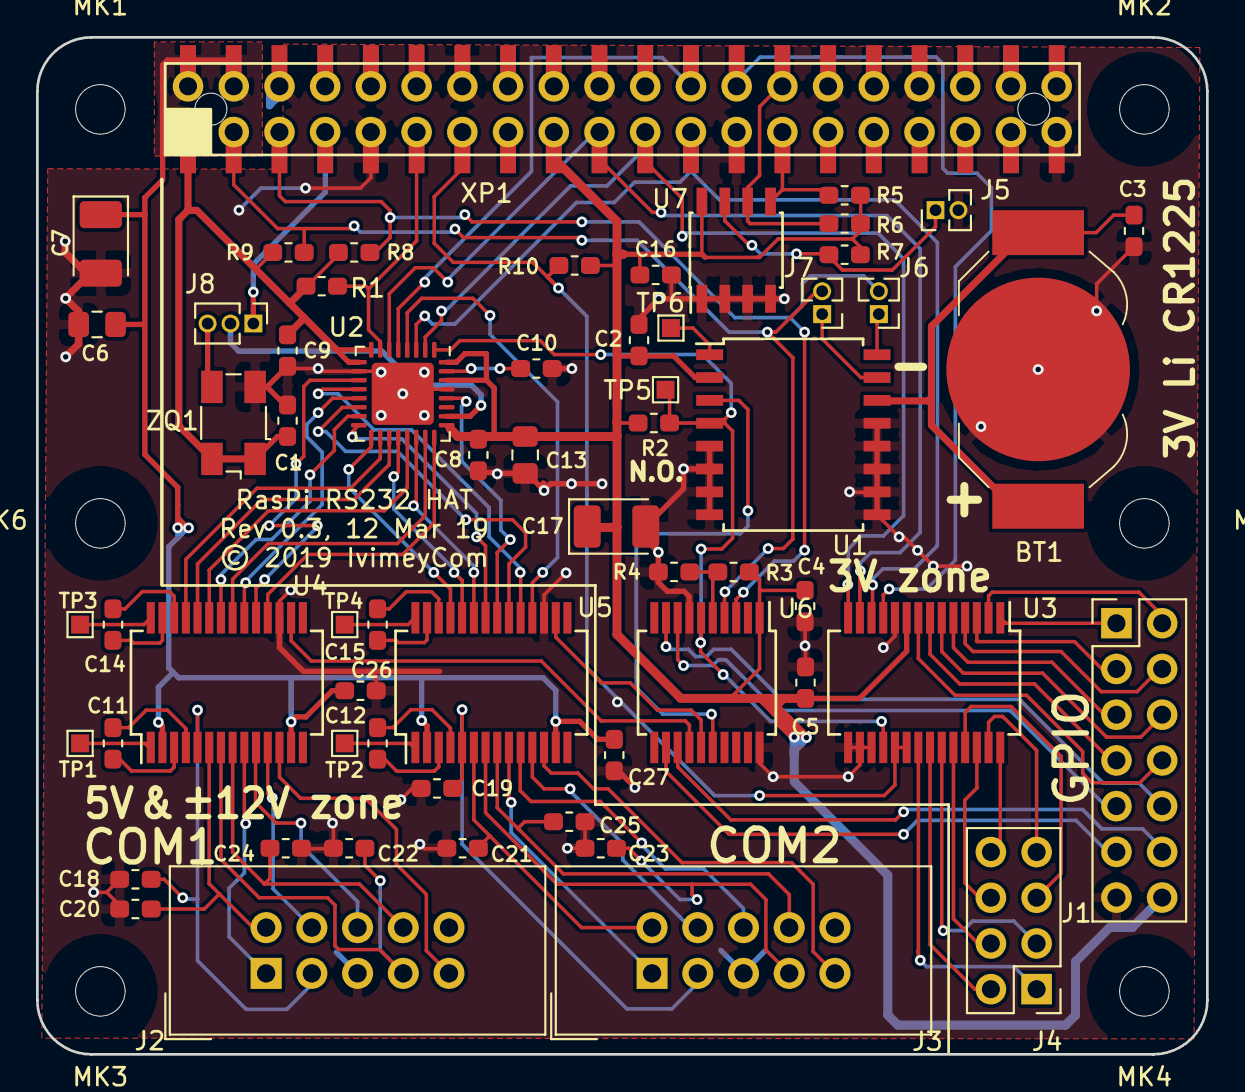
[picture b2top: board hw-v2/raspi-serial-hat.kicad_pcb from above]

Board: 2 copper layers, 65.0 x 56.5 mm, 67 parts (0 on the bottom side), 92 nets.

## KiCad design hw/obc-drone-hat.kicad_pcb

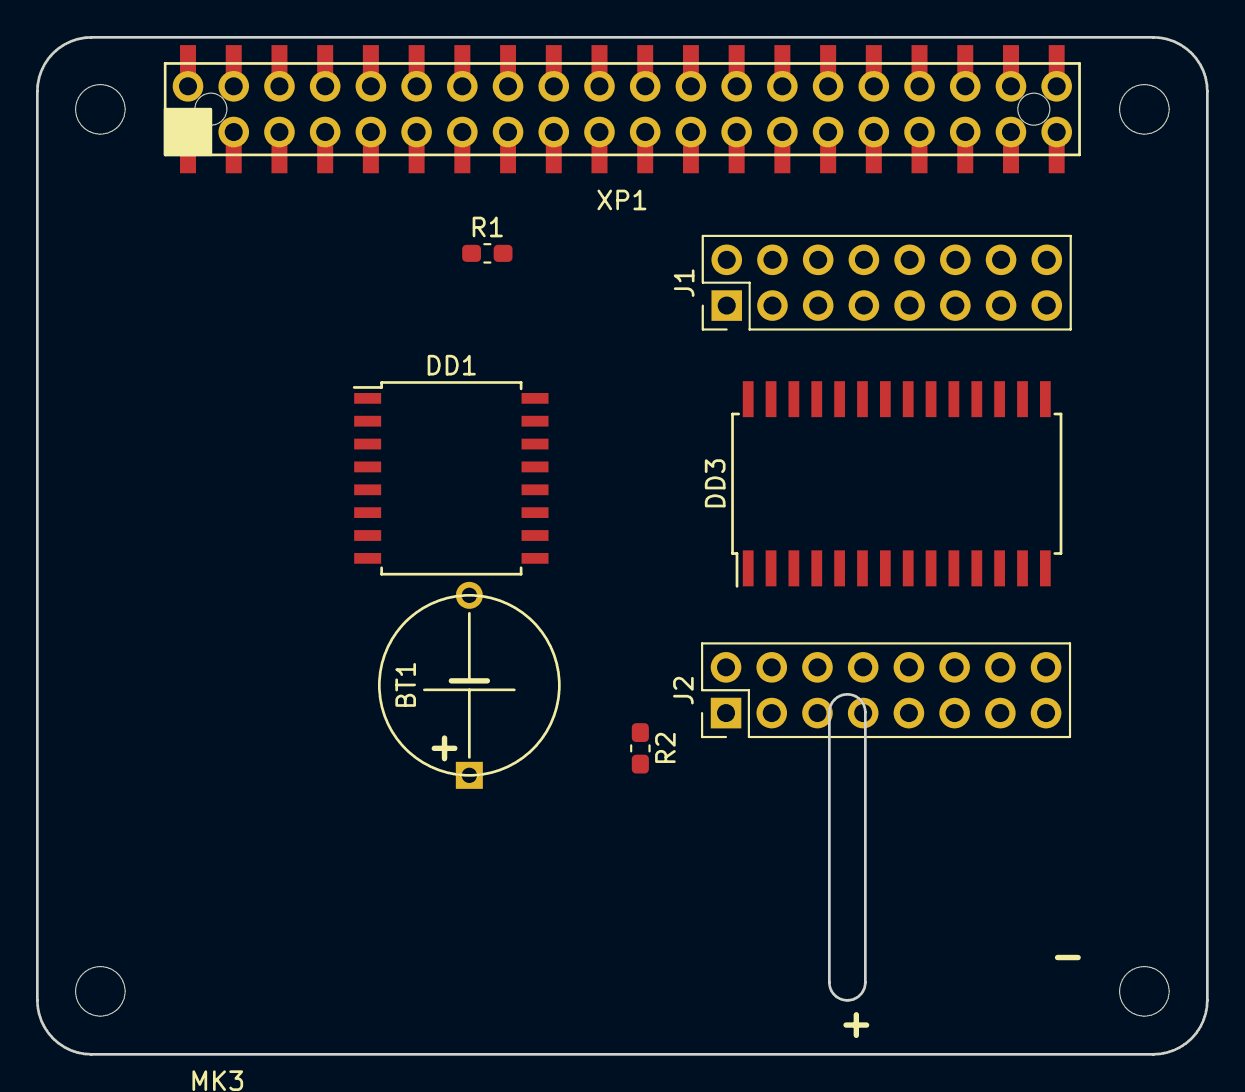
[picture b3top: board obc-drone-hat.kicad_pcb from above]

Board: 4 copper layers, 65.0 x 56.5 mm, 12 parts (0 on the bottom side), 30 nets.

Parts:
BT1: CR1225-VBY2
DD1: DS3231; SOIC-16W_7.5x10.3mm_P1.27mm
DD3: MCP23S17; SOIC-28W_7.5x17.9mm_P1.27mm
J1, J2: Conn_02x08_Top_Bottom; PinHeader_2x08_P2.54mm_Vertical
MK1, MK2, MK3, MK4: Mounting_Hole; M2.5_Mounting_Hole
R1: 10k; R_0603_1608Metric_Pad1.05x0.95mm_HandSolder
R2: nc; R_0603_1608Metric_Pad1.05x0.95mm_HandSolder
XP1: Rpi_40PIN; RaspberryPi-40Pin_P2.54mm

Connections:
+3V3: DD1.2, DD3.9, J1.10, J1.12, J1.14, J1.16, J2.10, J2.12, J2.14, J2.16, R1.2, R2.2, XP1.1, XP1.17
+5V: XP1.2, XP1.4
/+3Vbat: BT1.1, DD1.14
/CE1: DD3.11, XP1.26
GND: DD3.10, J1.9, J1.11, J1.13, J1.15, J2.9, J2.11, J2.13, J2.15, XP1.6, XP1.9, XP1.14, XP1.20, XP1.25, XP1.30, XP1.34, XP1.39
unnamed: BT1.2, DD1.13
unnamed: DD3.1, J2.8
unnamed: DD3.2, J2.7
unnamed: DD3.3, J2.6
unnamed: DD3.4, J2.5
unnamed: DD3.5, J2.4
unnamed: DD3.6, J2.3
unnamed: DD3.7, J2.2
unnamed: DD3.8, J2.1
unnamed: DD3.21, J1.8
unnamed: DD3.22, J1.7
unnamed: DD3.23, J1.6
unnamed: DD3.24, J1.5
unnamed: DD3.25, J1.4
unnamed: DD3.26, J1.3
unnamed: DD3.27, J1.2
unnamed: DD3.28, J1.1
RPI_SCL: DD1.16, XP1.5
RPI_SDA: DD1.15, XP1.3
RPI_SPI0_MISO: DD3.14, XP1.21
RPI_SPI0_MOSI: DD3.13, XP1.19
RPI_SPI0_SCLK: DD3.12, XP1.23
~HAT_RST: DD1.4, DD3.18, R2.1
~SER_IRQ_A: R1.1, XP1.11
~SER_IRQ_B: DD3.19, DD3.20

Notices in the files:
hw-v1/raspi-serial-hat.kicad_pcb:
(c) 2019 IvimeyCom
hw-v2/raspi-serial-hat.kicad_pcb:
© 2019 IvimeyCom
